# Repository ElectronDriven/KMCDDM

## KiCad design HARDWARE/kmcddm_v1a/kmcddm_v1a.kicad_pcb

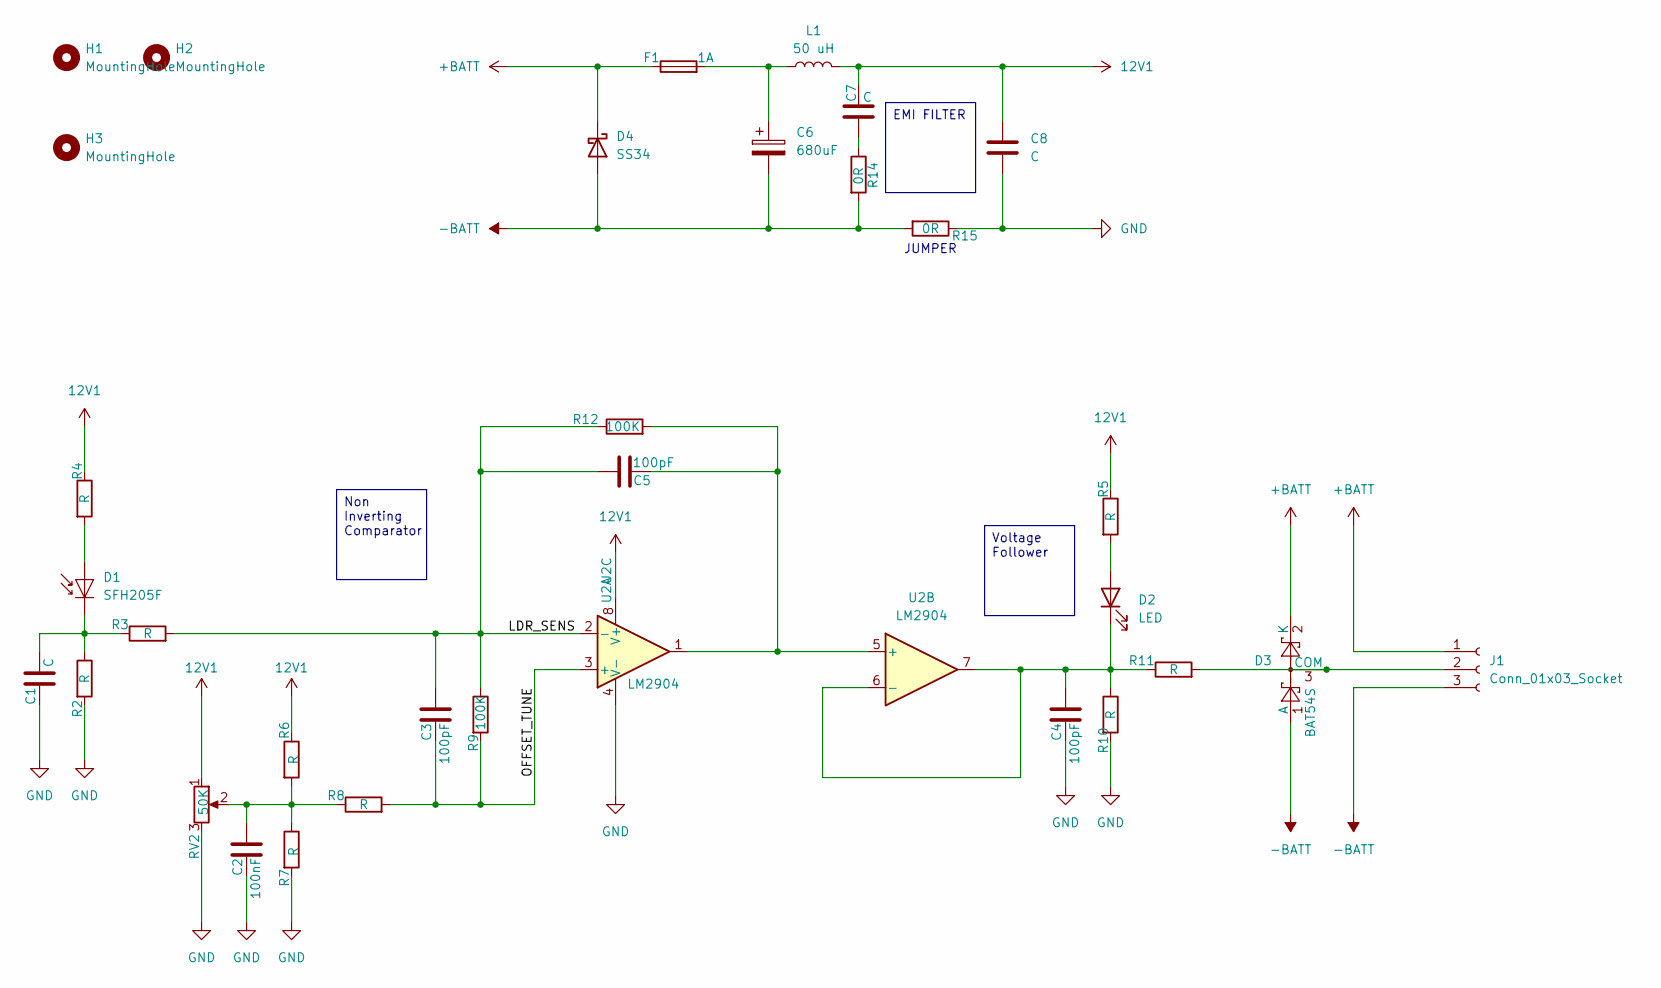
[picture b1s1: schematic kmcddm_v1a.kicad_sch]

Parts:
C1, C7: C; C_0603_1608Metric_Pad1.08x0.95mm_HandSolder
C2: 100nF; C_0603_1608Metric_Pad1.08x0.95mm_HandSolder
C3, C4, C5: 100pF; C_0603_1608Metric_Pad1.08x0.95mm_HandSolder
C6: 680uF; CP_Elec_4x4.5
C8: C; C_1206_3216Metric_Pad1.33x1.80mm_HandSolder
D1: SFH205F; Osram_SFH205
D2: LED; LED_1206_3216Metric
D3: BAT54S; SOT-23
D4: SS34; D_SMA
F1: 1A; Fuse_1206_3216Metric_Pad1.42x1.75mm_HandSolder
H1, H2, H3: MountingHole; MountingHole_2mm
J1: Conn_01x03_Socket; PinHeader_1x03_P2.00mm_Vertical
L1: 50 uH; L_1206_3216Metric_Pad1.42x1.75mm_HandSolder
R2, R3, R4, R5, R6, R7, R8, R10, R11: R; R_0603_1608Metric_Pad0.98x0.95mm_HandSolder
R9, R12: 100K; R_0603_1608Metric_Pad0.98x0.95mm_HandSolder
R14: 0R; R_0603_1608Metric_Pad0.98x0.95mm_HandSolder
R15: 0R; R_0402_1005Metric_Pad0.72x0.64mm_HandSolder
RV2: 50K; Potentiometer_Bourns_3314J_Vertical
U2: LM2904; SOIC-8_3.9x4.9mm_P1.27mm

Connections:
12V1: C7.1, C8.1, L1.2, R4.1, R5.1, R6.1, RV2.1, U2.8 (V+)
+BATT: D3.2 (K), D4.1 (K), F1.1, J1.1
-BATT: C6.2, D3.1 (A), D4.2 (A), J1.3, R14.2, R15.2
/LDR_SENS: C3.1, C5.1, R3.2, R9.1, R12.1, U2.2 (-)
/OFFSET_TUNE: C3.2, R8.2, R9.2, U2.3 (+)
GND: C1.2, C2.2, C4.2, C8.2, R2.2, R7.2, R10.2, R15.1, RV2.3, U2.4 (V-)
unnamed: C2.1, R6.2, R7.1, R8.1, RV2.2
unnamed: C6.1, F1.2, L1.1
unnamed: C7.2, R14.1
unnamed: D1.2 (A), R4.2
unnamed: C1.1, D1.1 (K), R2.1, R3.1
unnamed: D2.2 (A), R5.2
unnamed: C4.1, D2.1 (K), R10.1, R11.1, U2.6 (-), U2.7
unnamed: D3.3 (COM), J1.2, R11.2
unnamed: C5.2, R12.2, U2.1, U2.5 (+)

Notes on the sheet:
JUMPER
Voltage Follower
Non Inverting Comparator
EMI FILTER

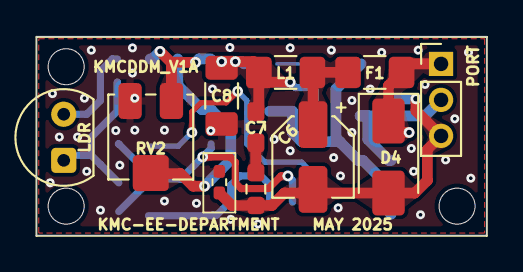
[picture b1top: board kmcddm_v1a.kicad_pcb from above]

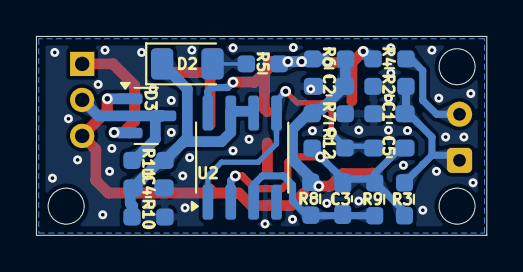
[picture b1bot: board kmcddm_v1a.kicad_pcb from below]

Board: 2 copper layers, 25.0 x 11.0 mm, 33 parts (19 on the bottom side), 15 nets.

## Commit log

2025-05-19 project repository is commited.
2025-05-19 project is ready to manufacture.
